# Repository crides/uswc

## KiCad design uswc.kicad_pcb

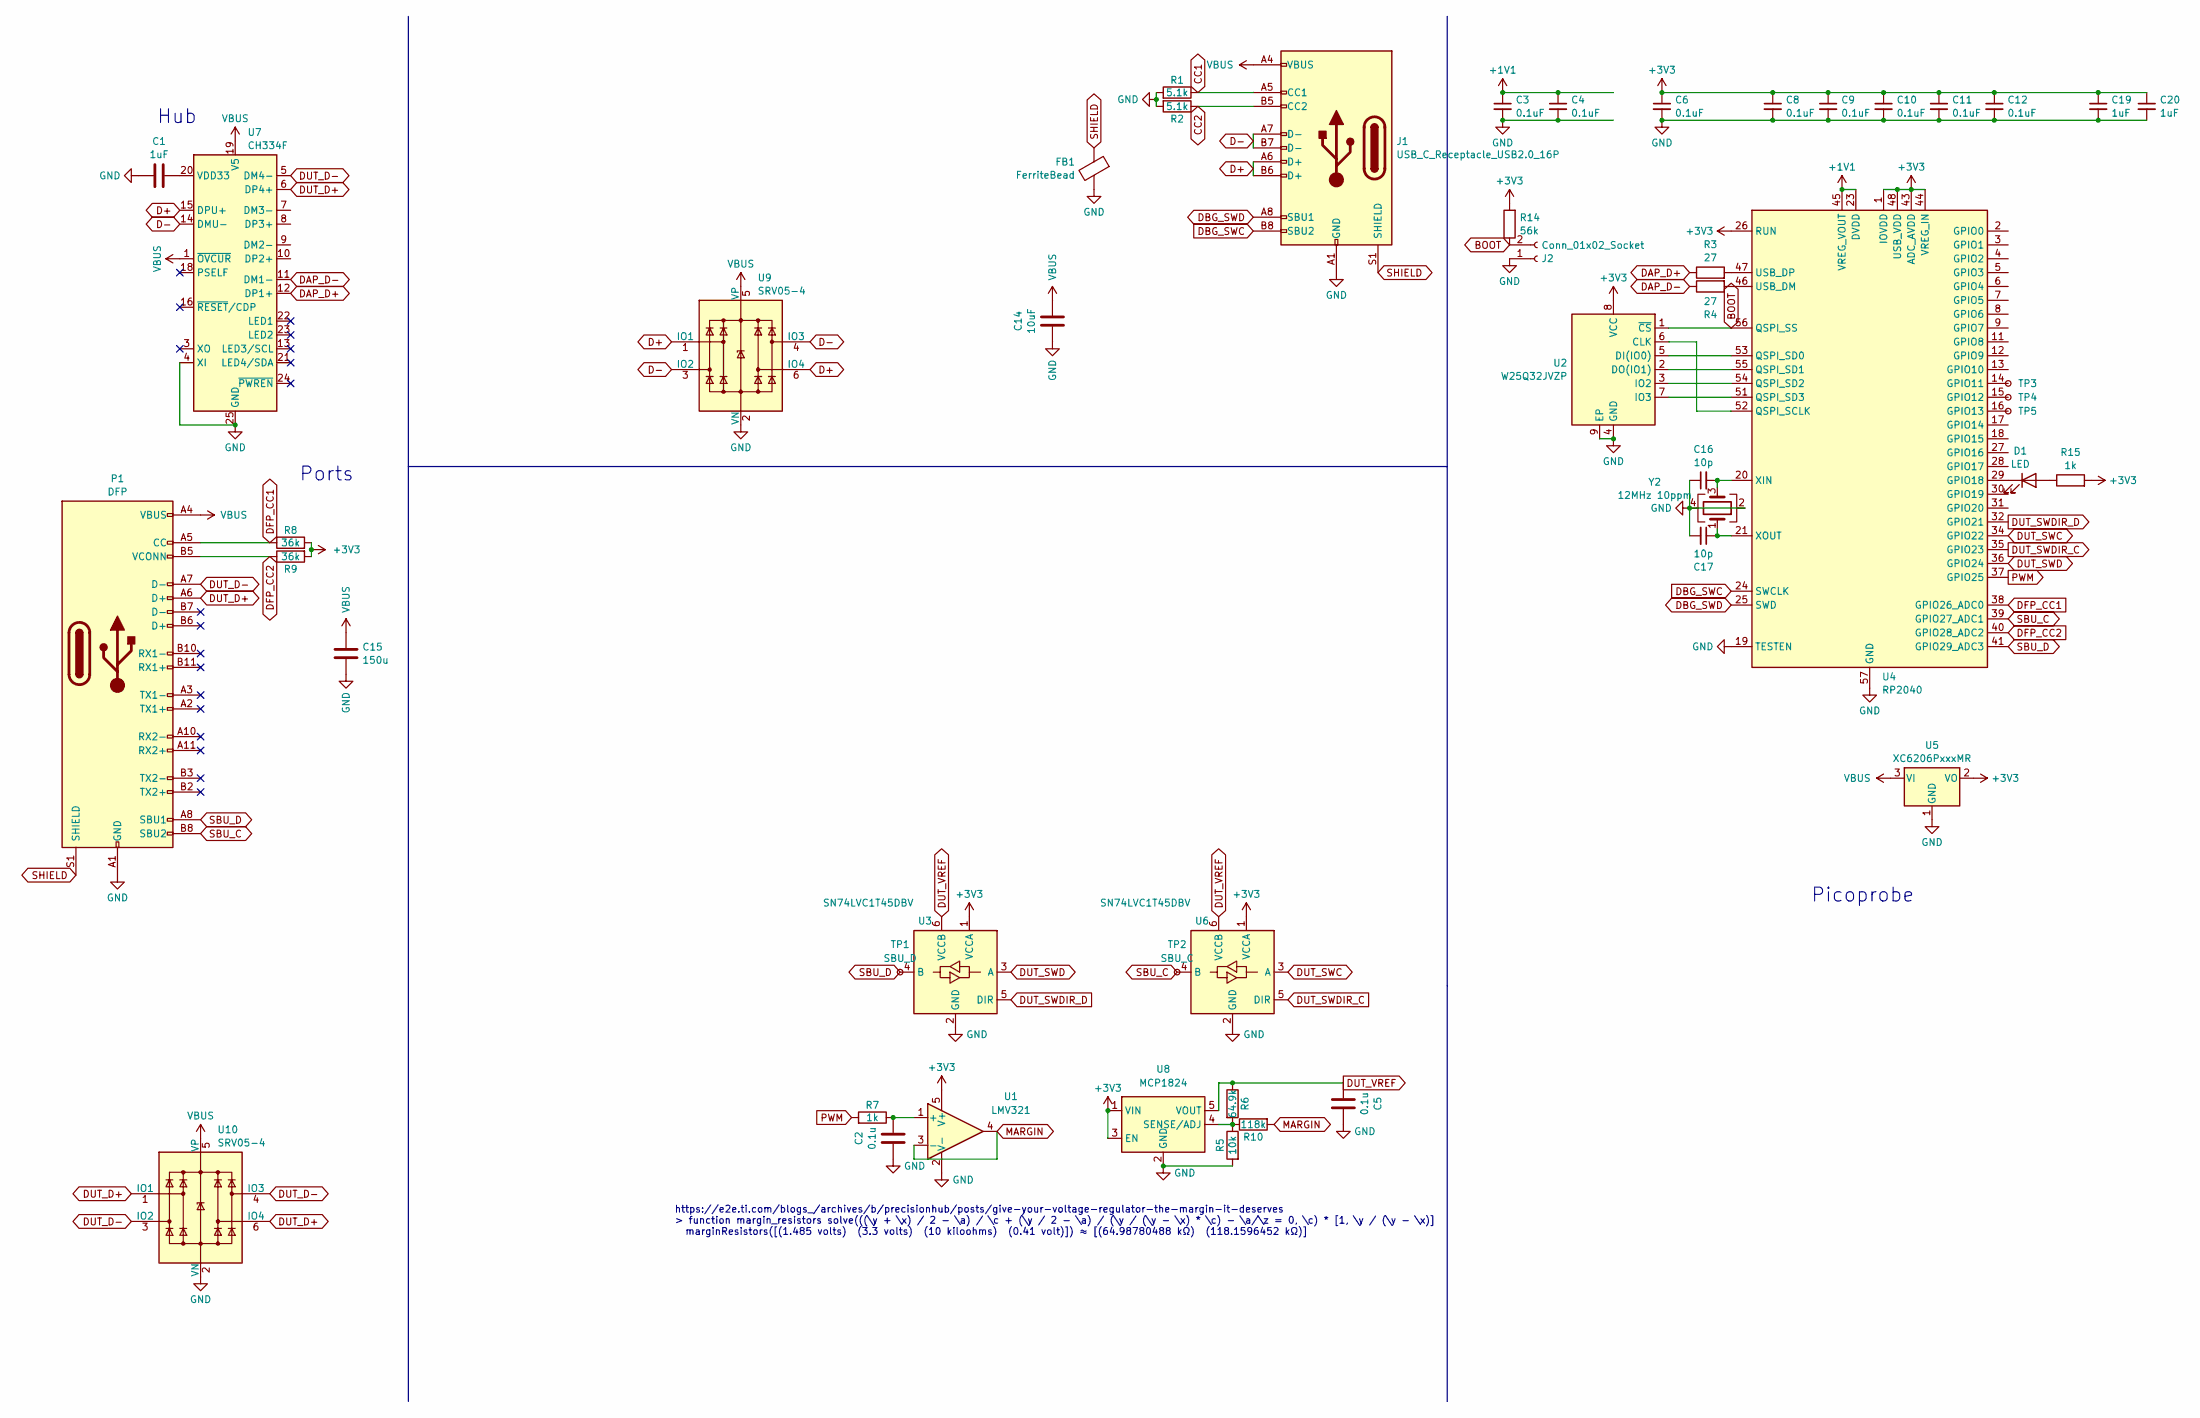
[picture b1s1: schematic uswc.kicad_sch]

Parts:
C1, C19, C20: 1uF; C_0603_1608Metric
C2, C5: 0.1u; C_0603_1608Metric
C3, C4, C6, C8, C9, C10, C11, C12: 0.1uF; C_0603_1608Metric
C14: 10uF; C_0603_1608Metric
C15: 150u; C_1206_3216Metric; LCSC# C528968
C16, C17: 10p; C_0603_1608Metric
D1: LED; LED_0805_2012Metric
FB1: FerriteBead; L_0805_2012Metric; LCSC# C1015
J1: USB_C_Receptacle_USB2.0_16P; USB_C_Receptacle_HRO_TYPE-C-31-M-12
J2: Conn_01x02_Socket; PinHeader_1x02_P2.00mm_Vertical
P1: DFP; jingtuojin_918-118A2021Y40005-no-ss; LCSC# C2763098
R1, R2: 5.1k; R_0603_1608Metric
R3, R4: 27; R_0603_1608Metric
R5: 10k; R_0603_1608Metric
R6: 64.9k; R_0603_1608Metric
R7, R15: 1k; R_0603_1608Metric
R8, R9: 36k; R_0603_1608Metric
R10: 118k; R_0603_1608Metric
R14: 56k; R_0603_1608Metric
TP1: SBU_D; TestPoint_Pad_D1.0mm
TP2: SBU_C; TestPoint_Pad_D1.0mm
TP3: -; TestPoint_Pad_D1.0mm
TP4, TP5: +; TestPoint_Pad_D1.0mm
U1: LMV321; SOT-353_SC-70-5
U2: W25Q32JVZP; Winbond_USON-8-1EP_3x2mm_P0.5mm_EP0.2x1.6mm
U3, U6: SN74LVC1T45DBV; SOT-363_SC-70-6; LCSC# C168856
U4: RP2040; QFN-56-1EP_7x7mm_P0.4mm_EP3.2x3.2mm
U5: XC6206PxxxMR; SOT-23-3
U7: CH334F; QFN-24-1EP_4x4mm_P0.5mm_EP2.7x2.7mm
U8: MCP1824; TSOT-23-5
U9, U10: SRV05-4; SOT-23-6
Y2: 12MHz 10ppm; Crystal_SMD_2016-4Pin_2.0x1.6mm

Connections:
+1V1: C3.1, C4.1, U4.23 (DVDD), U4.45 (VREG_VOUT), U4.50 (DVDD)
+3V3: C6.1, C8.1, C9.1, C10.1, C11.1, C12.1, C19.1, C20.1, R8.2, R9.2, R14.2, R15.2, U1.5 (V+), U2.8 (VCC), U3.1 (VCCA), U4.1 (IOVDD), U4.10 (IOVDD), U4.22 (IOVDD), U4.26 (RUN), U4.33 (IOVDD), U4.42 (IOVDD), U4.43 (ADC_AVDD), U4.44 (VREG_IN), U4.48 (USB_VDD), U4.49 (IOVDD), U5.2 (VO), U6.1 (VCCA), U8.1 (VIN), U8.3 (EN)
BOOT: J2.2, R14.1, U2.1 (~CS), U4.56 (QSPI_SS)
CC1: J1.A5 (CC1), R1.1
CC2: J1.B5 (CC2), R2.1
D+: J1.A6 (D+), J1.B6 (D+), U7.15 (DPU+), U9.1 (IO1), U9.6 (IO4)
D-: J1.A7 (D-), J1.B7 (D-), U7.14 (DMU-), U9.3 (IO2), U9.4 (IO3)
DAP_D+: R3.1, U7.12 (DP1+)
DAP_D-: R4.1, U7.11 (DM1-)
DBG_SWC: J1.B8 (SBU2), U4.24 (SWCLK)
DBG_SWD: J1.A8 (SBU1), U4.25 (SWD)
DFP_CC1: P1.A5 (CC), R8.1, U4.38 (GPIO26_ADC0)
DFP_CC2: P1.B5 (VCONN), R9.1, U4.40 (GPIO28_ADC2)
DUT_D+: P1.A6 (D+), U7.6 (DP4+), U10.1 (IO1), U10.6 (IO4)
DUT_D-: P1.A7 (D-), U7.5 (DM4-), U10.3 (IO2), U10.4 (IO3)
DUT_SWC: U4.34 (GPIO22), U6.3 (A)
DUT_SWD: U3.3 (A), U4.36 (GPIO24)
DUT_SWDIR_C: U4.35 (GPIO23), U6.5 (DIR)
DUT_SWDIR_D: U3.5 (DIR), U4.32 (GPIO21)
DUT_VREF: C5.1, R6.1, U3.6 (VCCB), U6.6 (VCCB), U8.5 (VOUT)
GND: C1.1, C2.2, C3.2, C4.2, C5.2, C6.2, C8.2, C9.2, C10.2, C11.2, C12.2, C14.2, C15.2, C16.1, C17.2, C19.2, C20.2, FB1.2, J1.A1 (GND), J1.A12 (GND), J1.B1 (GND), J1.B12 (GND), J2.1, P1.A1 (GND), P1.A12 (GND), P1.B1 (GND), P1.B12 (GND), R1.2, R2.2, R5.2, U1.2 (V-), U2.4 (GND), U2.9 (EP), U3.2 (GND), U4.19 (TESTEN), U4.57 (GND), U5.1 (GND), U6.2 (GND), U7.4 (XI), U7.25 (GND), U8.2 (GND), U9.2 (VN), U10.2 (VN), Y2.2, Y2.4
MARGIN: R10.2, U1.3 (-), U1.4
unnamed: D1.2 (A), R15.1
unnamed: D1.1 (K), U4.29 (GPIO18)
unnamed: C2.1, R7.1, U1.1 (+)
unnamed: U2.6 (CLK), U4.52 (QSPI_SCLK)
unnamed: U2.5 (DI(IO0)), U4.53 (QSPI_SD0)
unnamed: U2.2 (DO(IO1)), U4.55 (QSPI_SD1)
unnamed: U2.3 (IO2), U4.54 (QSPI_SD2)
unnamed: U2.7 (IO3), U4.51 (QSPI_SD3)
unnamed: TP3.1, U4.14 (GPIO11)
unnamed: TP4.1, U4.15 (GPIO12)
unnamed: TP5.1, U4.16 (GPIO13)
unnamed: R4.2, U4.46 (USB_DM)
unnamed: R3.2, U4.47 (USB_DP)
unnamed: C16.2, U4.20 (XIN), Y2.3
unnamed: C17.1, U4.21 (XOUT), Y2.1
unnamed: C1.2, U7.20 (VDD33)
unnamed: R5.1, R6.2, R10.1, U8.4 (SENSE/ADJ)
PWM: R7.2, U4.37 (GPIO25)
SBU_C: P1.B8 (SBU2), TP2.1, U4.39 (GPIO27_ADC1), U6.4 (B)
SBU_D: P1.A8 (SBU1), TP1.1, U3.4 (B), U4.41 (GPIO29_ADC3)
SHIELD: FB1.1, J1.S1 (SHIELD), P1.S1 (SHIELD)
VBUS: C14.1, C15.1, J1.A4 (VBUS), J1.A9 (VBUS), J1.B4 (VBUS), J1.B9 (VBUS), P1.A4 (VBUS), P1.A9 (VBUS), P1.B4 (VBUS), P1.B9 (VBUS), U5.3 (VI), U7.1 (~OVCUR), U7.19 (V5), U9.5 (VP), U10.5 (VP)

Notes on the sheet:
Ports
Hub
https://e2e.ti.com/blogs_/archives/b/precisionhub/posts/give-your-voltage-regulator-the-margin-it-deserves > function margin_resistors solve(((\y + \x) / 2 - \a) / \c + (\y / 2 - \a) / (\y / (\y - \x) * \c) - \a/\z = 0, \c) * [1, \y / (\y - \x)] marginResistors([(1.485 volts) (3.3 volts) (10 kilooh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
Picoprobe

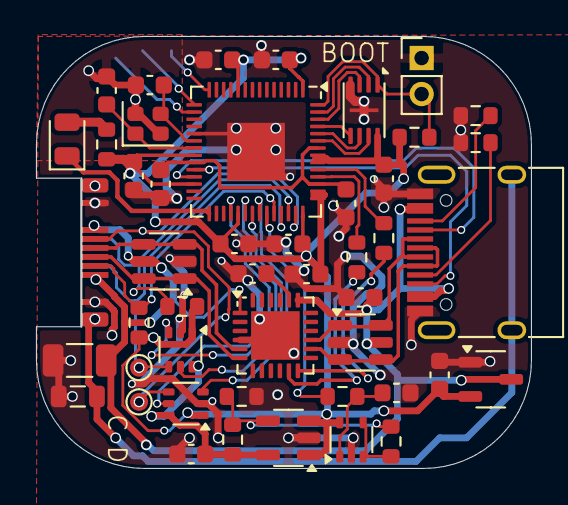
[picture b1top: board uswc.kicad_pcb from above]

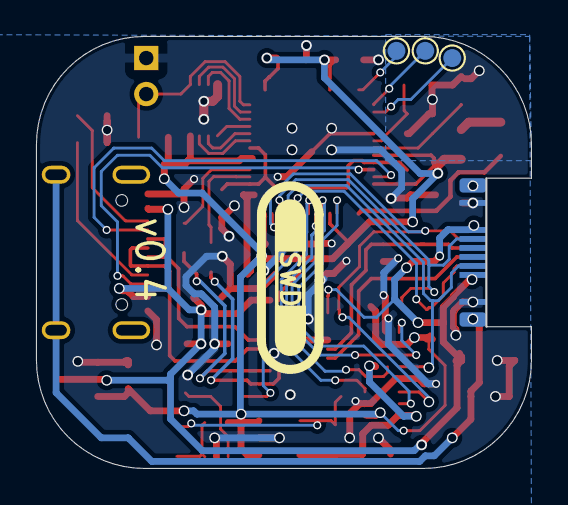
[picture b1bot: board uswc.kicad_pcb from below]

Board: 2 copper layers, 27.4 x 23.9 mm, 50 parts (3 on the bottom side), 44 nets.

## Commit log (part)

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2024-09-02 fab jingtuo
2024-09-02 fab 8012
2024-09-03 2 layer, analog switches
2024-11-24 pre level shifter
2024-11-24 pre only pico
2025-01-19 3d model
2025-02-09 backup
2025-08-29 pend
2025-10-08 v0.3
